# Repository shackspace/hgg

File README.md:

migrated to new location: https://codeberg.org/shackspace/hgg

hackerspace global grid
=======================

More documentation at [hgg.aero](http://hgg.aero/)

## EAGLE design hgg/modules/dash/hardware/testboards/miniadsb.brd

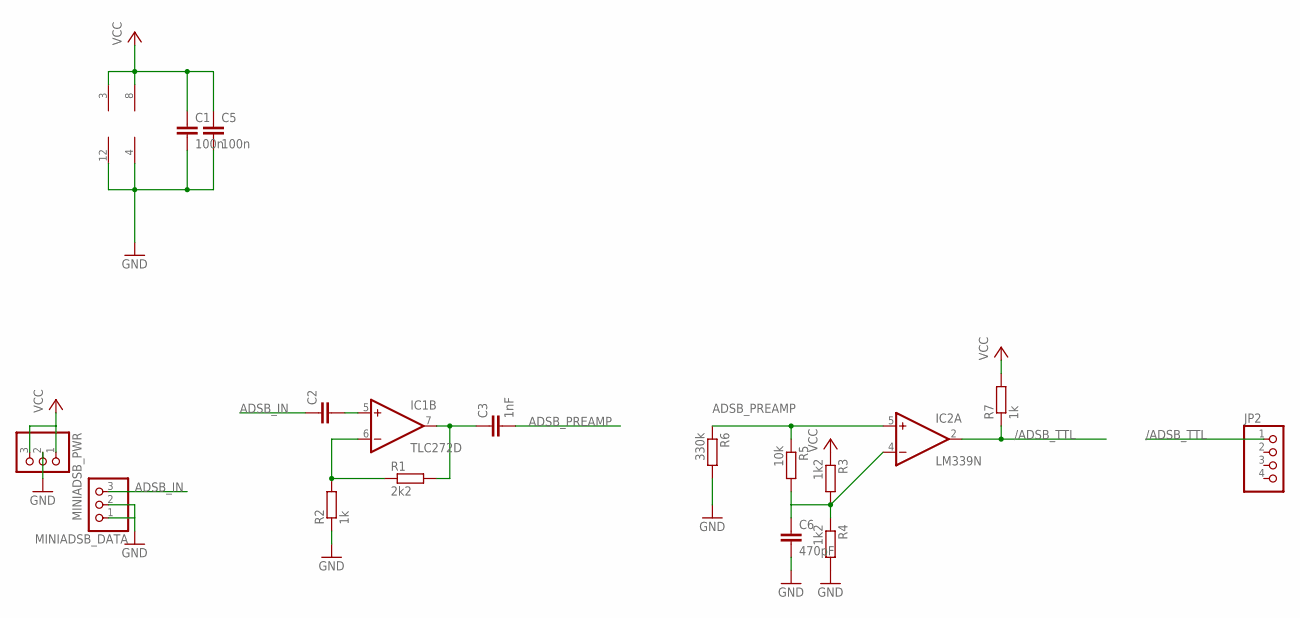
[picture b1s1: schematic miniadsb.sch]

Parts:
C1, C5: 100n; C0805
C2: C-EUC0805; C0805
C3: 1nF; C0805
C6: 470pF; C0805
IC1: TLC272D; SO08
IC2: LM339N; DIL14
JP2: PINHD-1X4; 1X04
MINIADSB_DATA: PINHD-1X3; 1X03
MINIADSB_PWR: PINHD-1X3; 1X03
R1: 2k2; R0805
R2: 1k; R0805
R3, R4: 1k2; R0805
R5: 10k; R0805
R6: 330k; R0805
R7: 1k; R0603

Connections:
/ADSB_TTL: IC2.2 (OUT), JP2.1, R7.1
ADSB_IN: C2.1, MINIADSB_DATA.3
ADSB_PREAMP: C3.2, IC2.5 (+IN), R5.1, R6.1
GND: C1.2, C5.2, C6.2, IC1.4 (V-), IC2.12 (GND), MINIADSB_DATA.1, MINIADSB_DATA.2, MINIADSB_PWR.2, R2.1, R4.2, R6.2
unnamed: C2.2, IC1.5 (+IN)
unnamed: C3.1, IC1.7 (OUT), R1.2
unnamed: IC1.6 (-IN), R1.1, R2.2
unnamed: C6.1, IC2.4 (-IN), R3.2, R4.1, R5.2
VCC: C1.1, C5.1, IC1.8 (V+), IC2.3 (V+), MINIADSB_PWR.1, MINIADSB_PWR.3, R3.1, R7.2

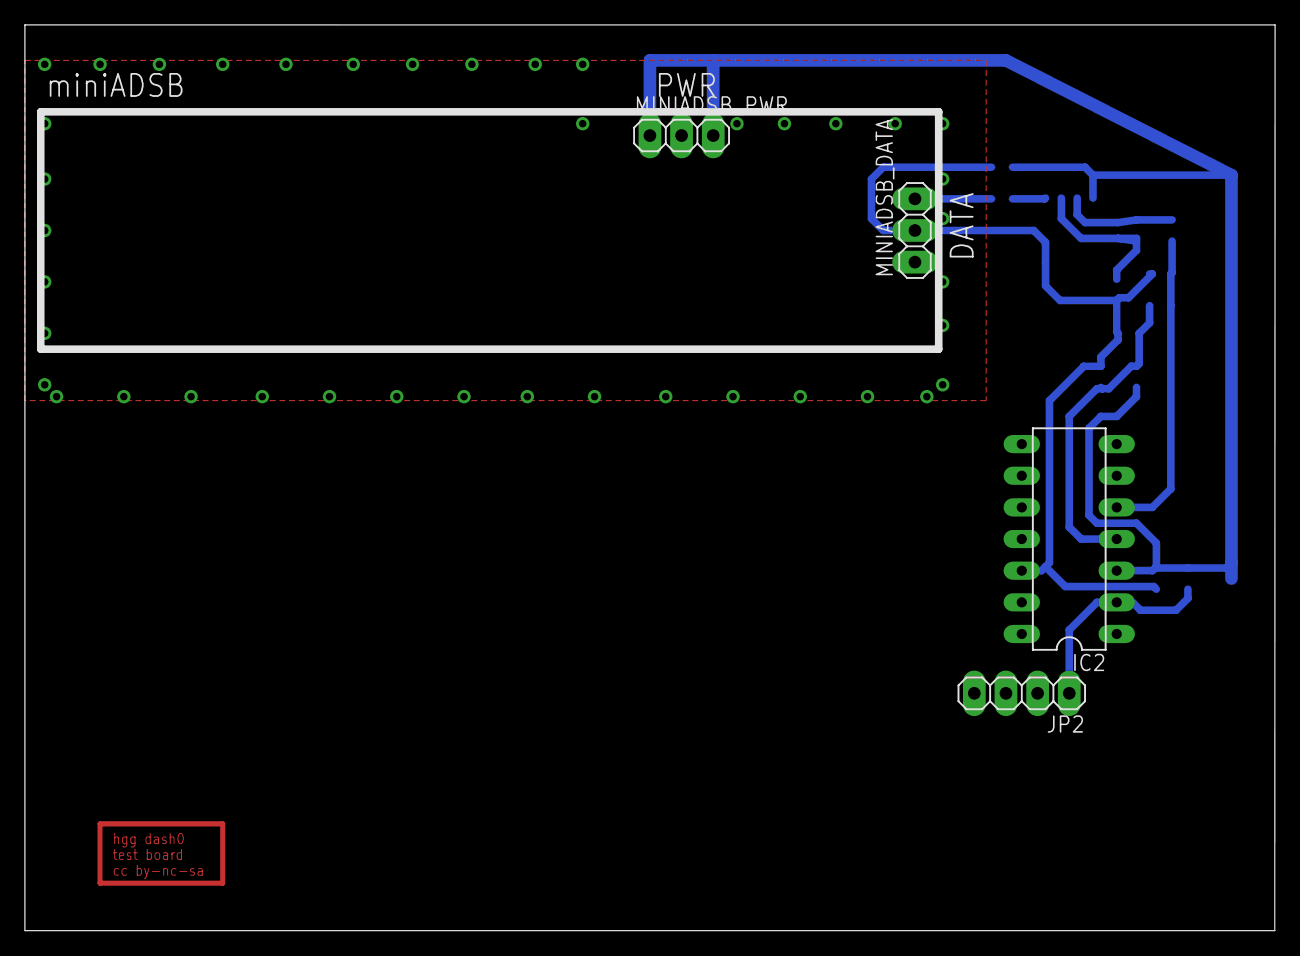
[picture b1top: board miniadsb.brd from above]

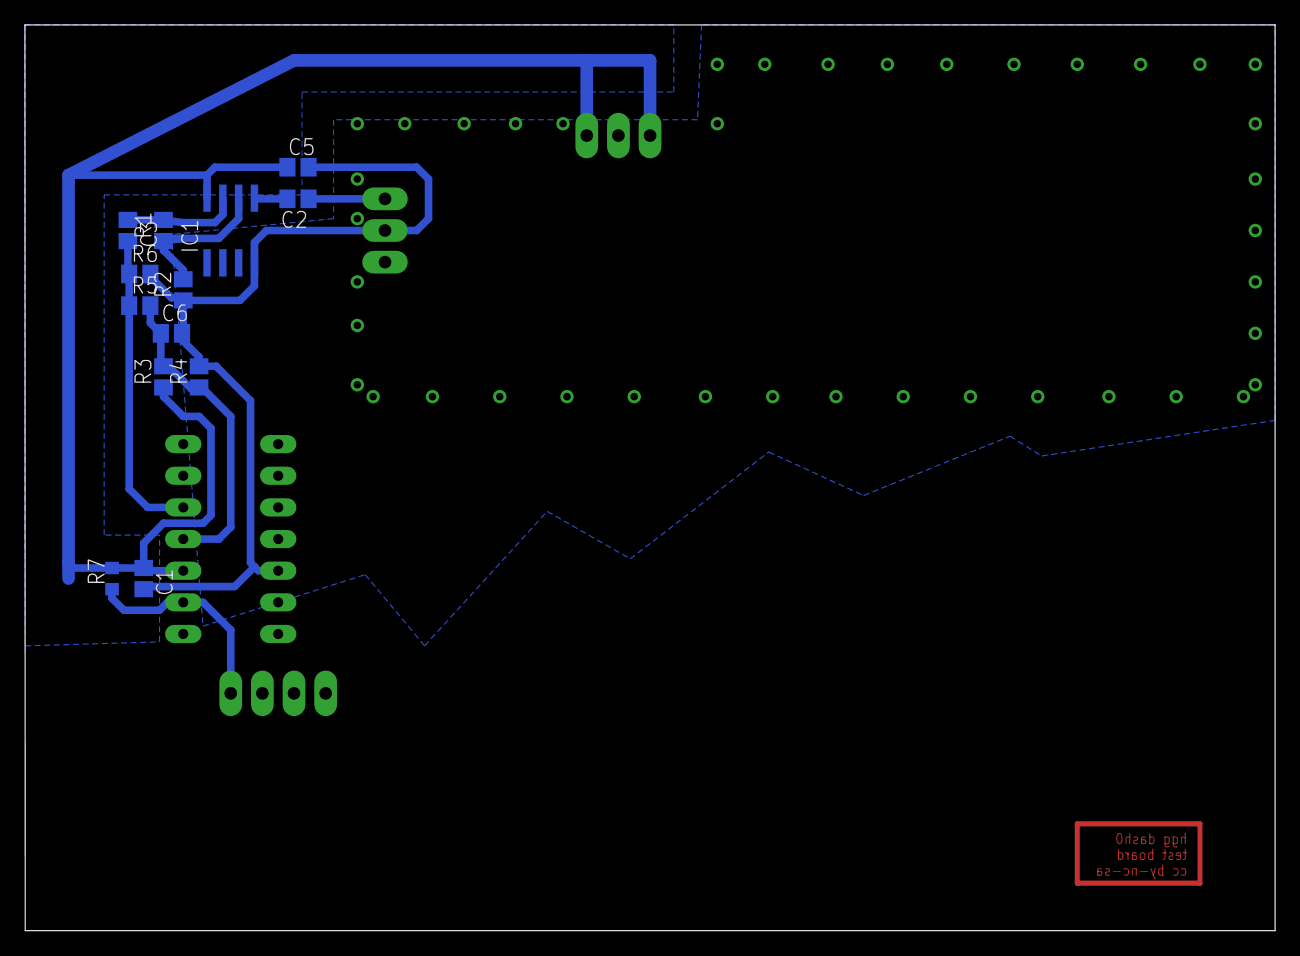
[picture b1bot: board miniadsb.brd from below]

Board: 2 copper layers, 100.3 x 72.7 mm, 17 parts (13 on the bottom side), 9 nets.

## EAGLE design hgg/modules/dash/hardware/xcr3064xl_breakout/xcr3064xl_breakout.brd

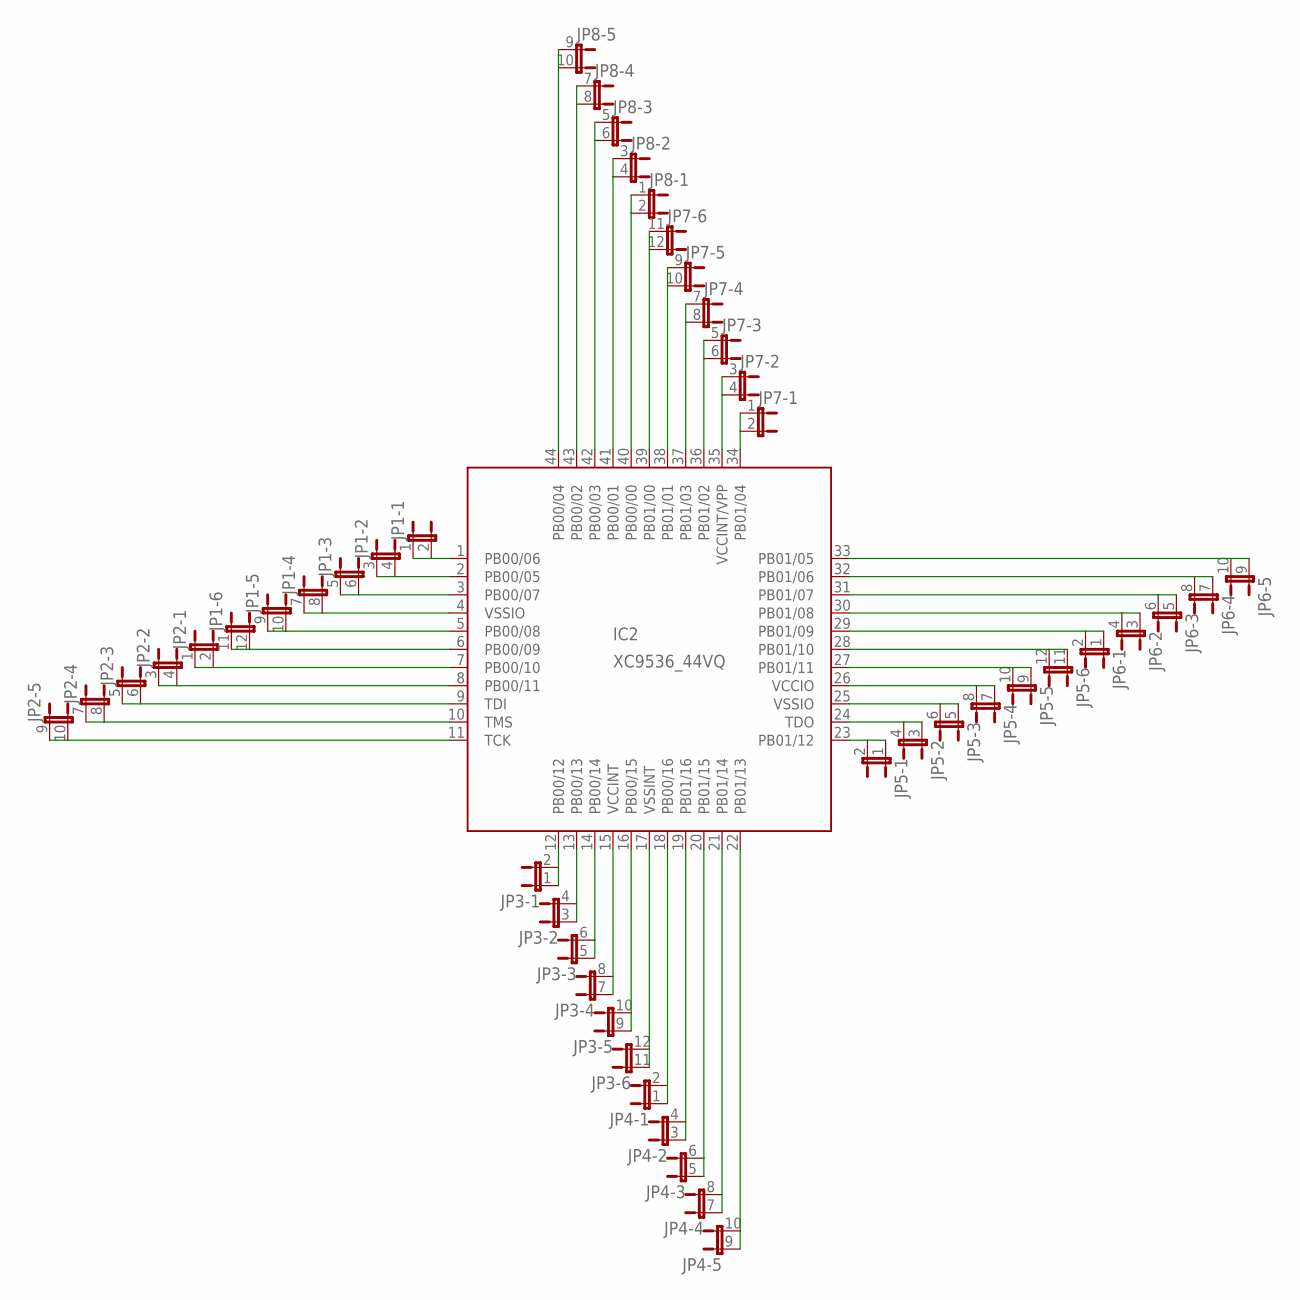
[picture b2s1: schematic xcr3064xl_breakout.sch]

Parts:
IC2: XC9536_44VQ; SQFP-S-10X10-44
JP1, JP2, JP3, JP4, JP5, JP6, JP7, JP8: JP6QE; JP6Q

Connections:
unnamed: IC2.1 (PB00/06), JP1.1, JP1.2
unnamed: IC2.2 (PB00/05), JP1.3 (1), JP1.4 (2)
unnamed: IC2.3 (PB00/07), JP1.5 (1), JP1.6 (2)
unnamed: IC2.4 (VSSIO), JP1.7 (1), JP1.8 (2)
unnamed: IC2.5 (PB00/08), JP1.9 (1), JP1.10 (2)
unnamed: IC2.6 (PB00/09), JP1.11 (1), JP1.12 (2)
unnamed: IC2.7 (PB00/10), JP2.1, JP2.2
unnamed: IC2.8 (PB00/11), JP2.3 (1), JP2.4 (2)
unnamed: IC2.9 (TDI), JP2.5 (1), JP2.6 (2)
unnamed: IC2.10 (TMS), JP2.7 (1), JP2.8 (2)
unnamed: IC2.11 (TCK), JP2.9 (1), JP2.10 (2)
unnamed: IC2.12 (PB00/12), JP3.1, JP3.2
unnamed: IC2.13 (PB00/13), JP3.3 (1), JP3.4 (2)
unnamed: IC2.14 (PB00/14), JP3.5 (1), JP3.6 (2)
unnamed: IC2.15 (VCCINT), JP3.7 (1), JP3.8 (2)
unnamed: IC2.16 (PB00/15), JP3.9 (1), JP3.10 (2)
unnamed: IC2.17 (VSSINT), JP3.11 (1), JP3.12 (2)
unnamed: IC2.18 (PB00/16), JP4.1, JP4.2
unnamed: IC2.19 (PB01/16), JP4.3 (1), JP4.4 (2)
unnamed: IC2.20 (PB01/15), JP4.5 (1), JP4.6 (2)
unnamed: IC2.21 (PB01/14), JP4.7 (1), JP4.8 (2)
unnamed: IC2.22 (PB01/13), JP4.9 (1), JP4.10 (2)
unnamed: IC2.23 (PB01/12), JP5.1, JP5.2
unnamed: IC2.24 (TDO), JP5.3 (1), JP5.4 (2)
unnamed: IC2.25 (VSSIO), JP5.5 (1), JP5.6 (2)
unnamed: IC2.26 (VCCIO), JP5.7 (1), JP5.8 (2)
unnamed: IC2.27 (PB01/11), JP5.9 (1), JP5.10 (2)
unnamed: IC2.28 (PB01/10), JP5.11 (1), JP5.12 (2)
unnamed: IC2.29 (PB01/09), JP6.1, JP6.2
unnamed: IC2.30 (PB01/08), JP6.3 (1), JP6.4 (2)
unnamed: IC2.31 (PB01/07), JP6.5 (1), JP6.6 (2)
unnamed: IC2.32 (PB01/06), JP6.7 (1), JP6.8 (2)
unnamed: IC2.33 (PB01/05), JP6.9 (1), JP6.10 (2)
unnamed: IC2.34 (PB01/04), JP7.1, JP7.2
unnamed: IC2.35 (VCCINT/VPP), JP7.3 (1), JP7.4 (2)
unnamed: IC2.36 (PB01/02), JP7.5 (1), JP7.6 (2)
unnamed: IC2.37 (PB01/03), JP7.7 (1), JP7.8 (2)
unnamed: IC2.38 (PB01/01), JP7.9 (1), JP7.10 (2)
unnamed: IC2.39 (PB01/00), JP7.11 (1), JP7.12 (2)
unnamed: IC2.40 (PB00/00), JP8.1, JP8.2
unnamed: IC2.41 (PB00/01), JP8.3 (1), JP8.4 (2)
unnamed: IC2.42 (PB00/03), JP8.5 (1), JP8.6 (2)
unnamed: IC2.43 (PB00/02), JP8.7 (1), JP8.8 (2)
unnamed: IC2.44 (PB00/04), JP8.9 (1), JP8.10 (2)

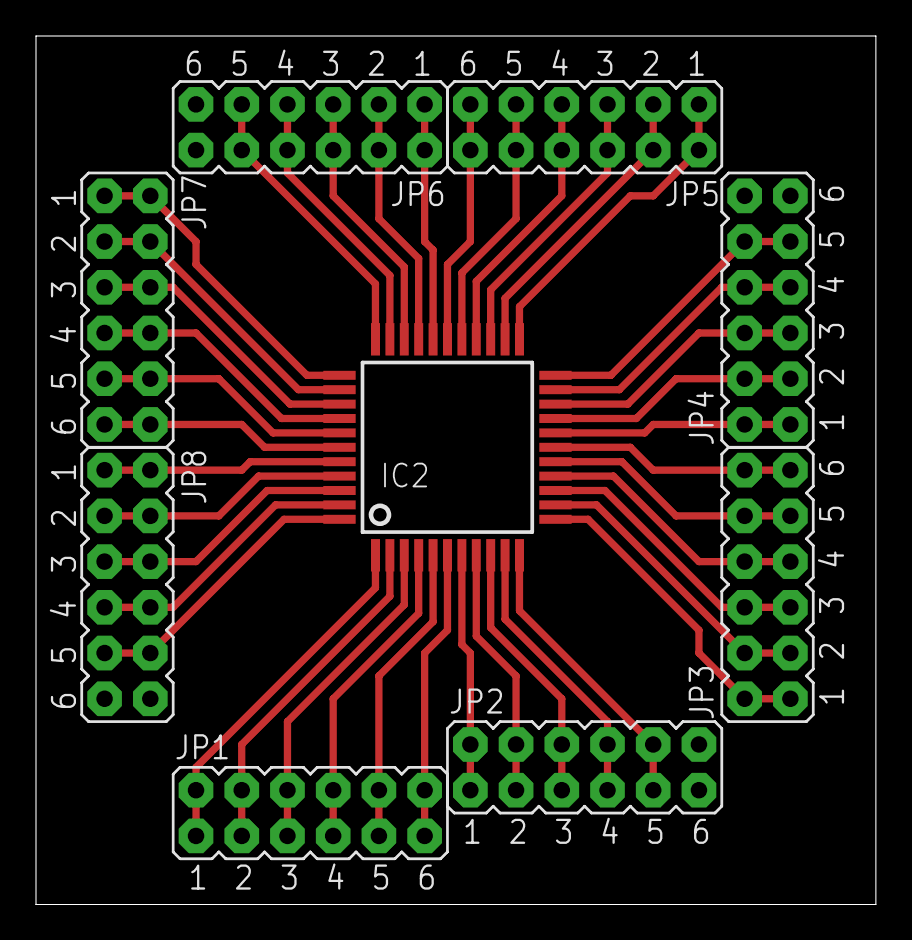
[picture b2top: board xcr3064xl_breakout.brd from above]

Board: 2 copper layers, 46.7 x 48.2 mm, 9 parts (0 on the bottom side), 44 nets.

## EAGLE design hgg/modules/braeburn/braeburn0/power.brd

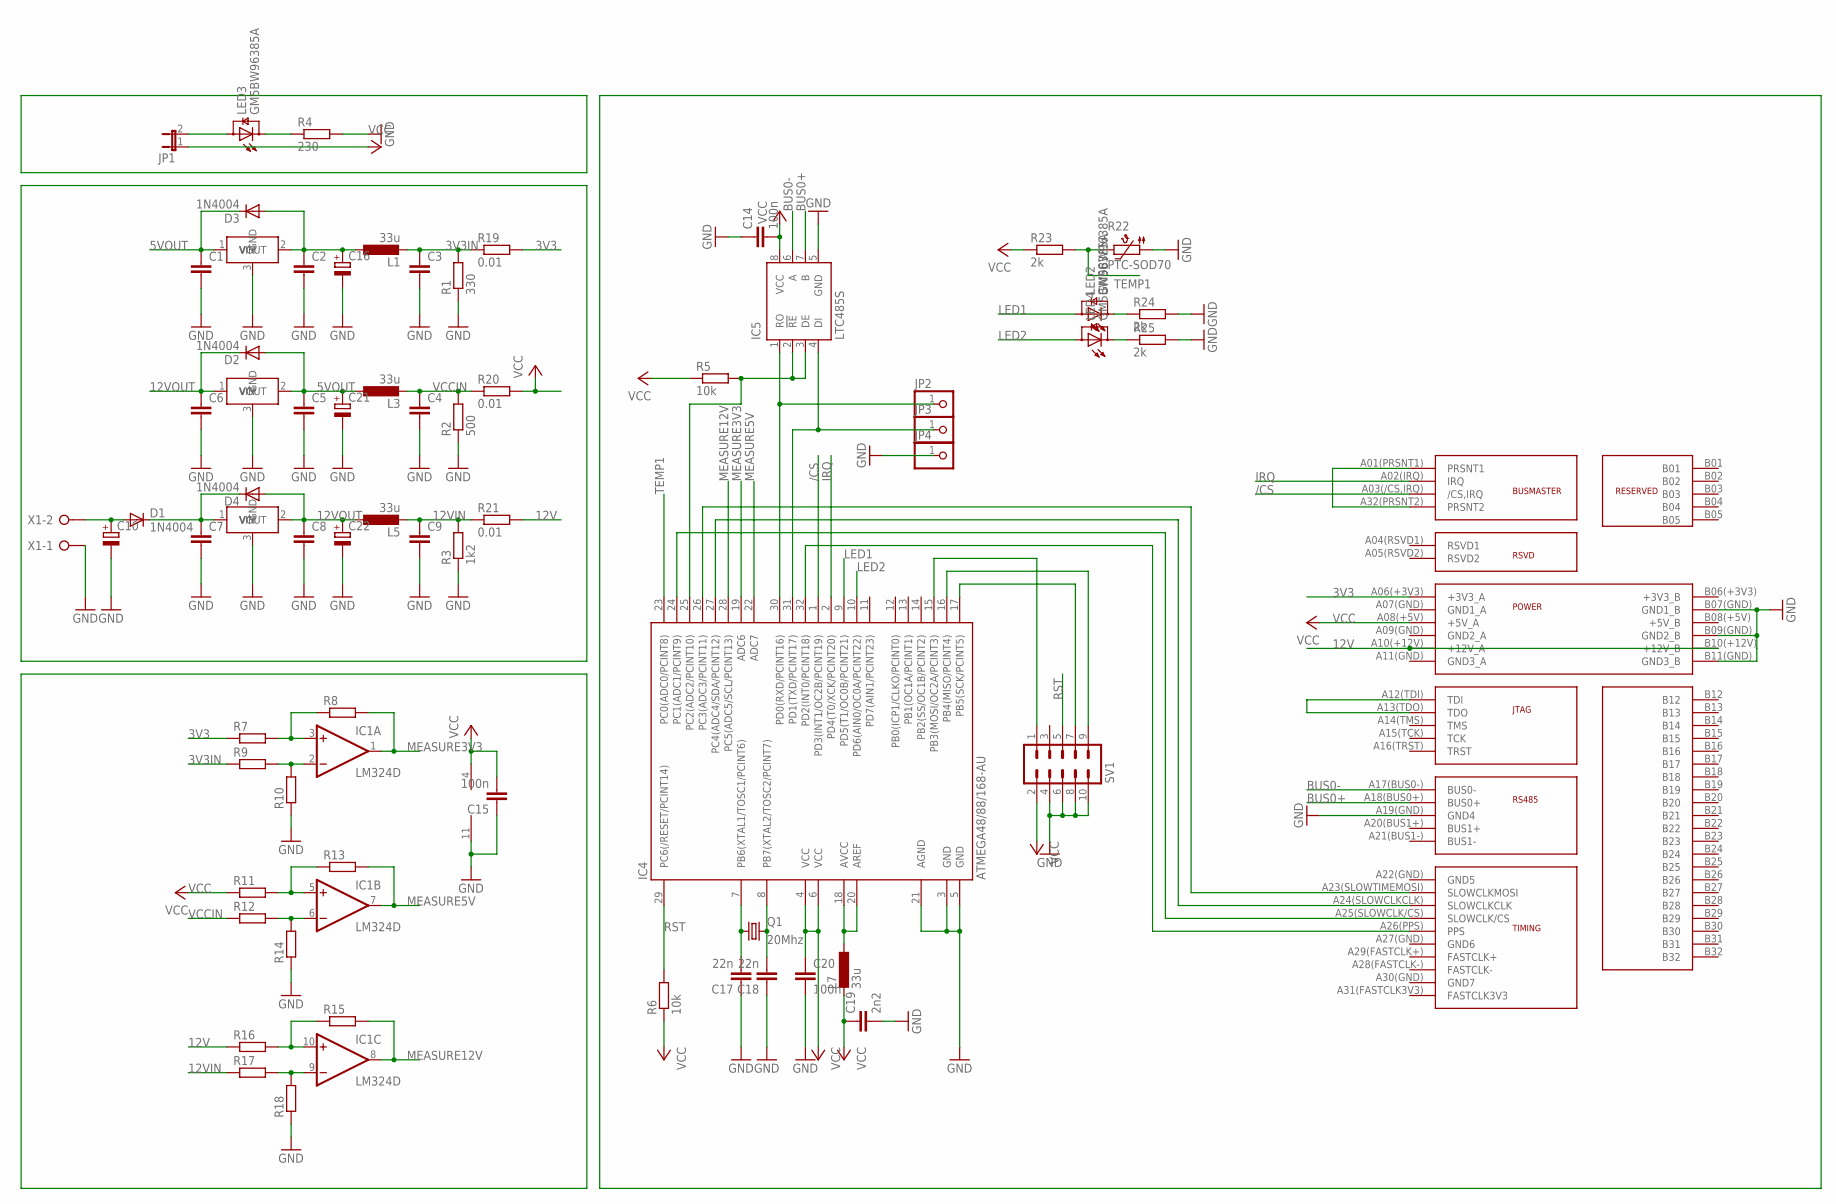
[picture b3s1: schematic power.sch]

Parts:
C1, C2, C3, C4, C5, C6, C7, C8, C9: C-EUC0805; C0805
C10: CPOL-EU150CLZ-1010; 150CLZ-1010
C14, C15, C20: 100n; C0603
C16, C21, C22: CPOL-EU153CLV-0505; 153CLV-0505
C17, C18: 22n; C0603
C19: 2n2; C0603
D1, D2, D3, D4: 1N4004; DO41-10
IC1: LM324D; SO14
IC4: ATMEGA48/88/168-AU; TQFP32-08
IC5: LTC485S; SOIC8
JP1: JP1E; JP1
JP2, JP3, JP4: PINHD-1X1; 1X01
L1, L3, L5, L7: 33u; 0207/5V
LED2, LED3, LED4: GM5BW96385A
Q1: 20Mhz; HC49UP
R1: 330; R0805
R2: 500; R0603
R3: 1k2; R0603
R4: 230; R0603
R5, R6: 10k; R0603
R7, R8, R9, R10, R11, R12, R13, R14, R15, R16, R17, R18: R-EU_R0603; R0603
R19, R20, R21: 0.01; 0207/15
R22: PTC-SOD70; SOD70
R23, R24, R25: 2k; R0603
SV1: MA05-2
U$1: FRIENDSHIPCONNECTOR; FRIENDSHIP_EDGE_CONNECTOR
U$2, U$3, U$4: AP1084; TO263
X1: W237-02P; W237-132

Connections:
3V3: R7.1, R19.2, U$1.A06(+3V3) (+3V3_A)
3V3IN: C3.1, L1.2, R1.2, R9.1, R19.1
5VOUT: C1.1, C5.1, C21.+, D2.A, D3.C, L3.1, U$2.1 (VIN), U$3.2 (VOUT)
12V: R16.1, R21.2, U$1.A10(+12V) (+12V_A), U$1.B10(+12V) (+12V_B)
12VIN: C9.1, L5.2, R3.2, R17.1, R21.1
12VOUT: C6.1, C8.1, C22.+, D2.C, D4.A, L5.1, U$3.1 (VIN), U$4.2 (VOUT)
/CS: IC4.1 (PD3(INT1/OC2B/PCINT19)), U$1.A03(/CS,IRQ) (/CS,IRQ)
BUS0+: IC5.7 (B), U$1.A18(BUS0+) (BUS0+)
BUS0-: IC5.6 (A), U$1.A17(BUS0-) (BUS0-)
GND: C1.2, C2.2, C3.2, C4.2, C5.2, C6.2, C7.2, C8.2, C9.2, C10.-, C14.1, C15.1, C16.-, C17.1, C18.1, C19.2, C20.2, C21.-, C22.-, IC1.11 (V-), IC4.3 (GND), IC4.5 (GND), IC4.21 (AGND), IC5.5 (GND), JP4.1, R1.1, R2.1, R3.1, R4.2, R10.1, R14.1, R18.1, R22.1, R24.2, R25.2, SV1.4, SV1.6, SV1.8, SV1.10, U$1.A19(GND) (GND4), U$1.B07(GND) (GND1_B), U$1.B09(GND) (GND2_B), U$1.B11(GND) (GND3_B), U$2.3 (GND), U$3.3 (GND), U$4.3 (GND), X1.1
IRQ: IC4.2 (PD4(T0/XCK/PCINT20)), U$1.A02(IRQ) (IRQ)
LED1: IC4.9 (PD5(T1/OC0B/PCINT21)), LED2.A
LED2: IC4.10 (PD6(AIN0/OC0A/PCINT22)), LED4.A
MEASURE3V3: IC1.1 (OUT), IC4.19 (ADC6), R8.2
MEASURE5V: IC1.7 (OUT), IC4.22 (ADC7), R13.2
MEASURE12V: IC1.8 (OUT), IC4.28 (PC5(ADC5/SCL/PCINT13)), R15.2
unnamed: C18.2, IC4.8 (PB7(XTAL2/TOSC2/PCINT7)), Q1.2
unnamed: C2.1, C16.+, D3.A, L1.1, U$2.2 (VOUT)
unnamed: IC4.24 (PC1(ADC1/PCINT9)), U$1.A25(SLOWCLK/CS) (SLOWCLK/CS)
unnamed: IC1.2 (-IN), R9.2, R10.2
unnamed: IC1.3 (+IN), R7.2, R8.1
unnamed: JP1.2, LED3.A
unnamed: C7.1, D1.C, D4.C, U$4.1 (VIN)
unnamed: C10.+, D1.A, X1.2
unnamed: C17.2, IC4.7 (PB6(XTAL1/TOSC1/PCINT6)), Q1.1
unnamed: IC1.6 (-IN), R12.2, R14.2
unnamed: IC4.18 (AVCC), IC4.20 (AREF), L7.1
unnamed: IC4.16 (PB4(MISO/PCINT4)), SV1.9
unnamed: IC4.17 (PB5(SCK/PCINT5)), SV1.7
unnamed: IC4.15 (PB3(MOSI/OC2A/PCINT3)), SV1.1
unnamed: LED3.C, R4.1
unnamed: IC4.32 (PD2(INT0/PCINT18)), U$1.A26(PPS) (PPS)
unnamed: IC4.31 (PD1(TXD/PCINT17)), IC5.4 (DI), JP3.1
unnamed: IC1.5 (+IN), R11.2, R13.1
unnamed: U$1.A01(PRSNT1) (PRSNT1), U$1.A32(PRSNT2) (PRSNT2)
unnamed: IC4.27 (PC4(ADC4/SDA/PCINT12)), U$1.A24(SLOWCLKCLK) (SLOWCLKCLK)
unnamed: IC4.26 (PC3(ADC3/PCINT11)), U$1.A23(SLOWTIMEMOSI) (SLOWCLKMOSI)
unnamed: IC1.10 (+IN), R15.1, R16.2
unnamed: IC1.9 (-IN), R17.2, R18.2
unnamed: U$1.A12(TDI) (TDI), U$1.A13(TDO) (TDO)
unnamed: IC4.30 (PD0(RXD/PCINT16)), IC5.1 (RO), JP2.1
unnamed: IC4.25 (PC2(ADC2/PCINT10)), IC5.2 (!RE), IC5.3 (DE), R5.2
unnamed: LED2.C, R24.1
unnamed: LED4.C, R25.1
RST: IC4.29 (PC6(/RESET/PCINT14)), R6.2, SV1.5
TEMP1: IC4.23 (PC0(ADC0/PCINT8)), R22.2, R23.2
VCC: C14.2, C15.2, C19.1, C20.1, IC1.4 (V+), IC4.4 (VCC), IC4.6 (VCC), IC5.8 (VCC), JP1.1, L7.2, R5.1, R6.1, R11.1, R20.2, R23.1, SV1.2, U$1.A08(+5V) (+5V_A)
VCCIN: C4.1, L3.2, R2.2, R12.1, R20.1

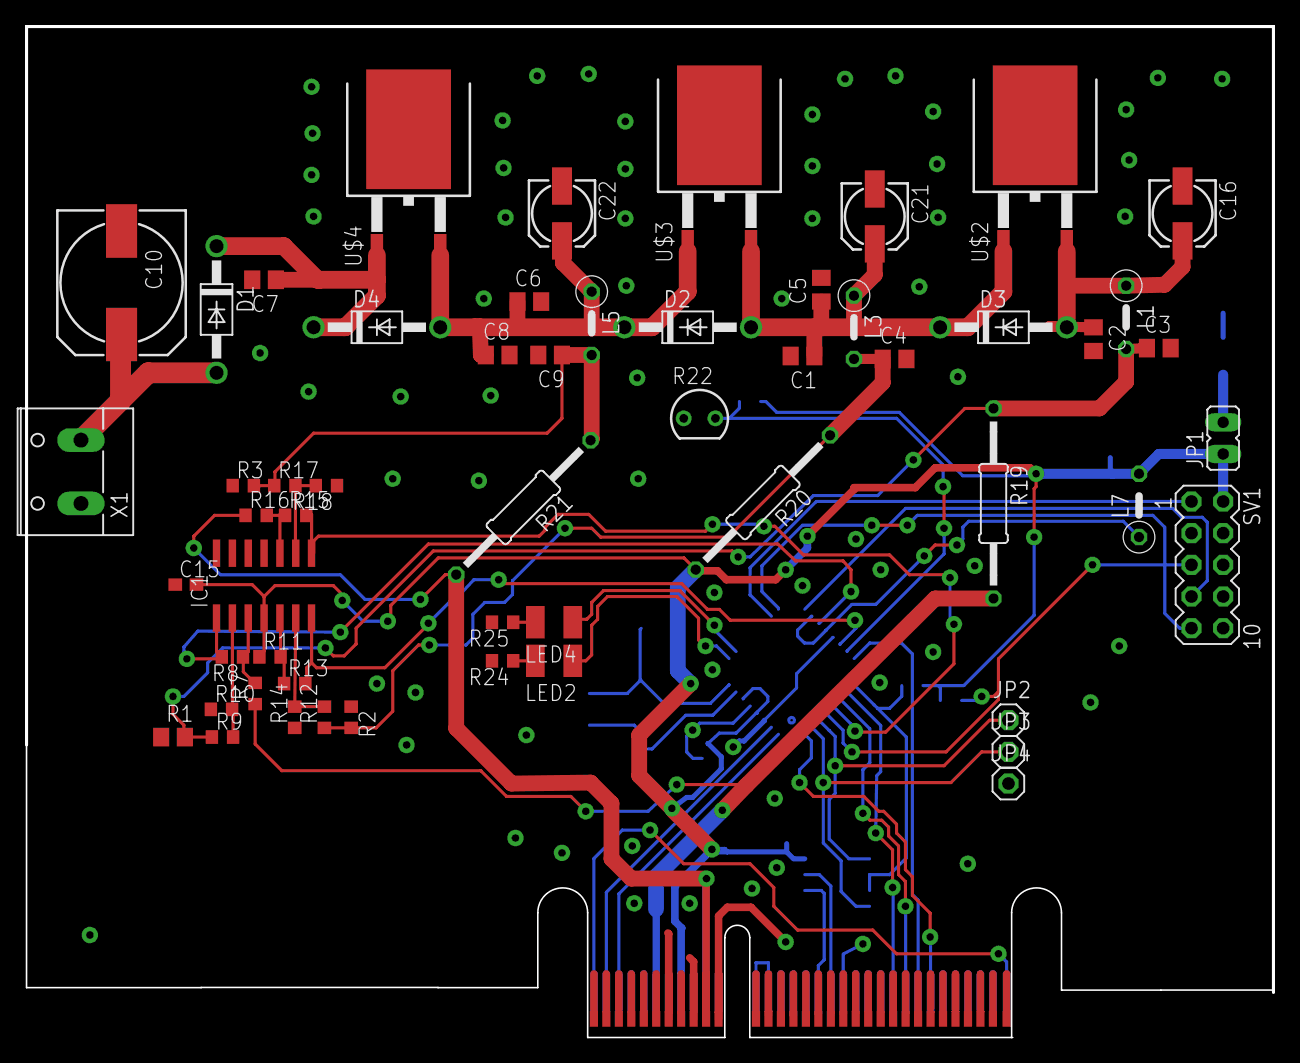
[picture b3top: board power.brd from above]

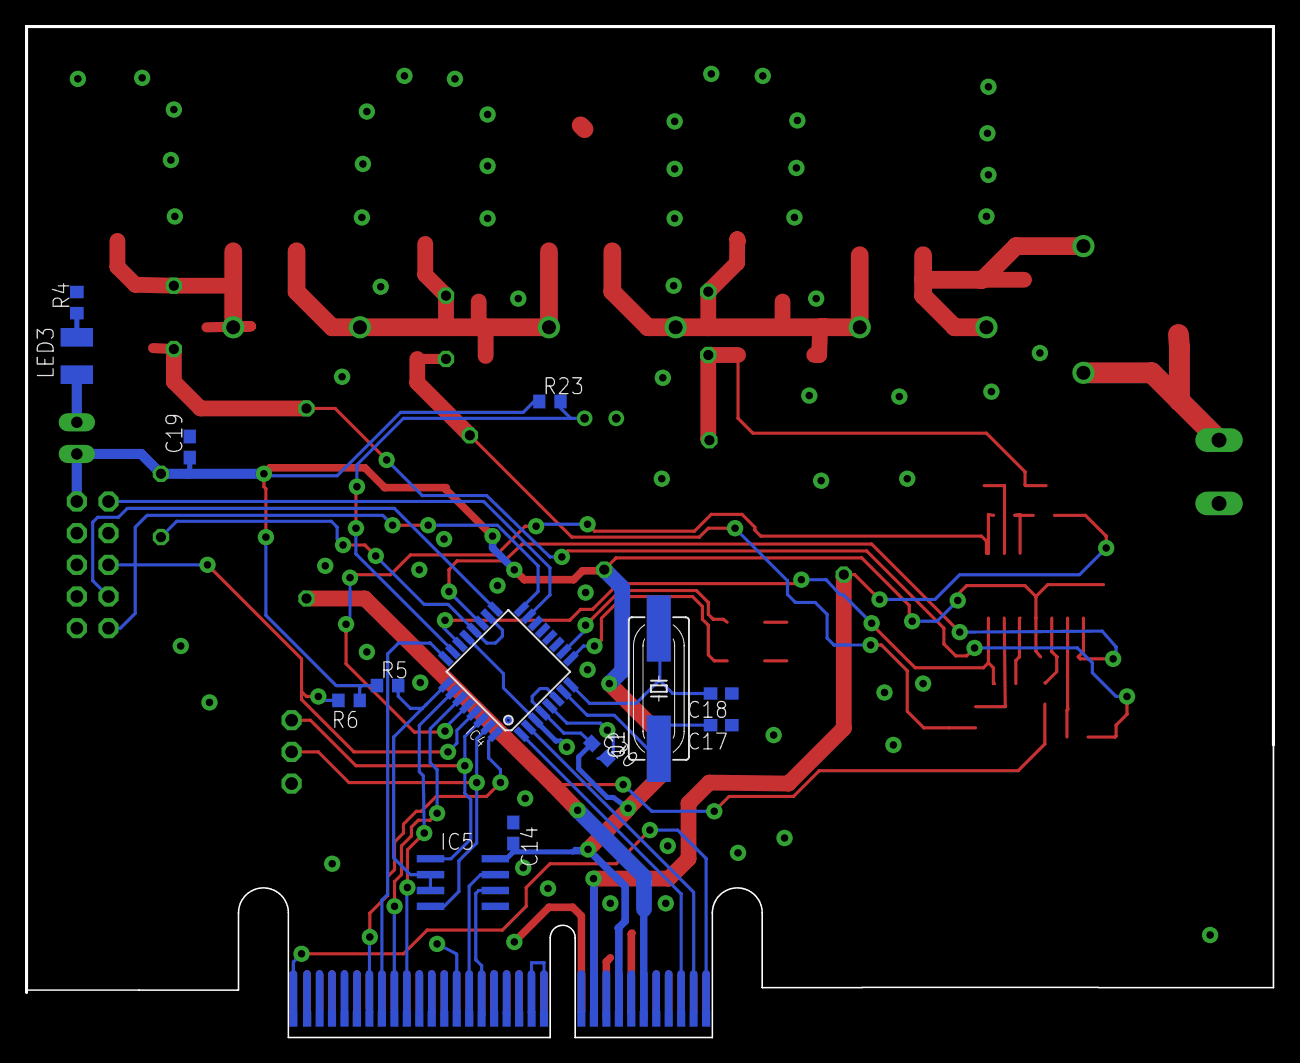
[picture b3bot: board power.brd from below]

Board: 2 copper layers, 100.0 x 81.1 mm, 69 parts (13 on the bottom side), 48 nets.

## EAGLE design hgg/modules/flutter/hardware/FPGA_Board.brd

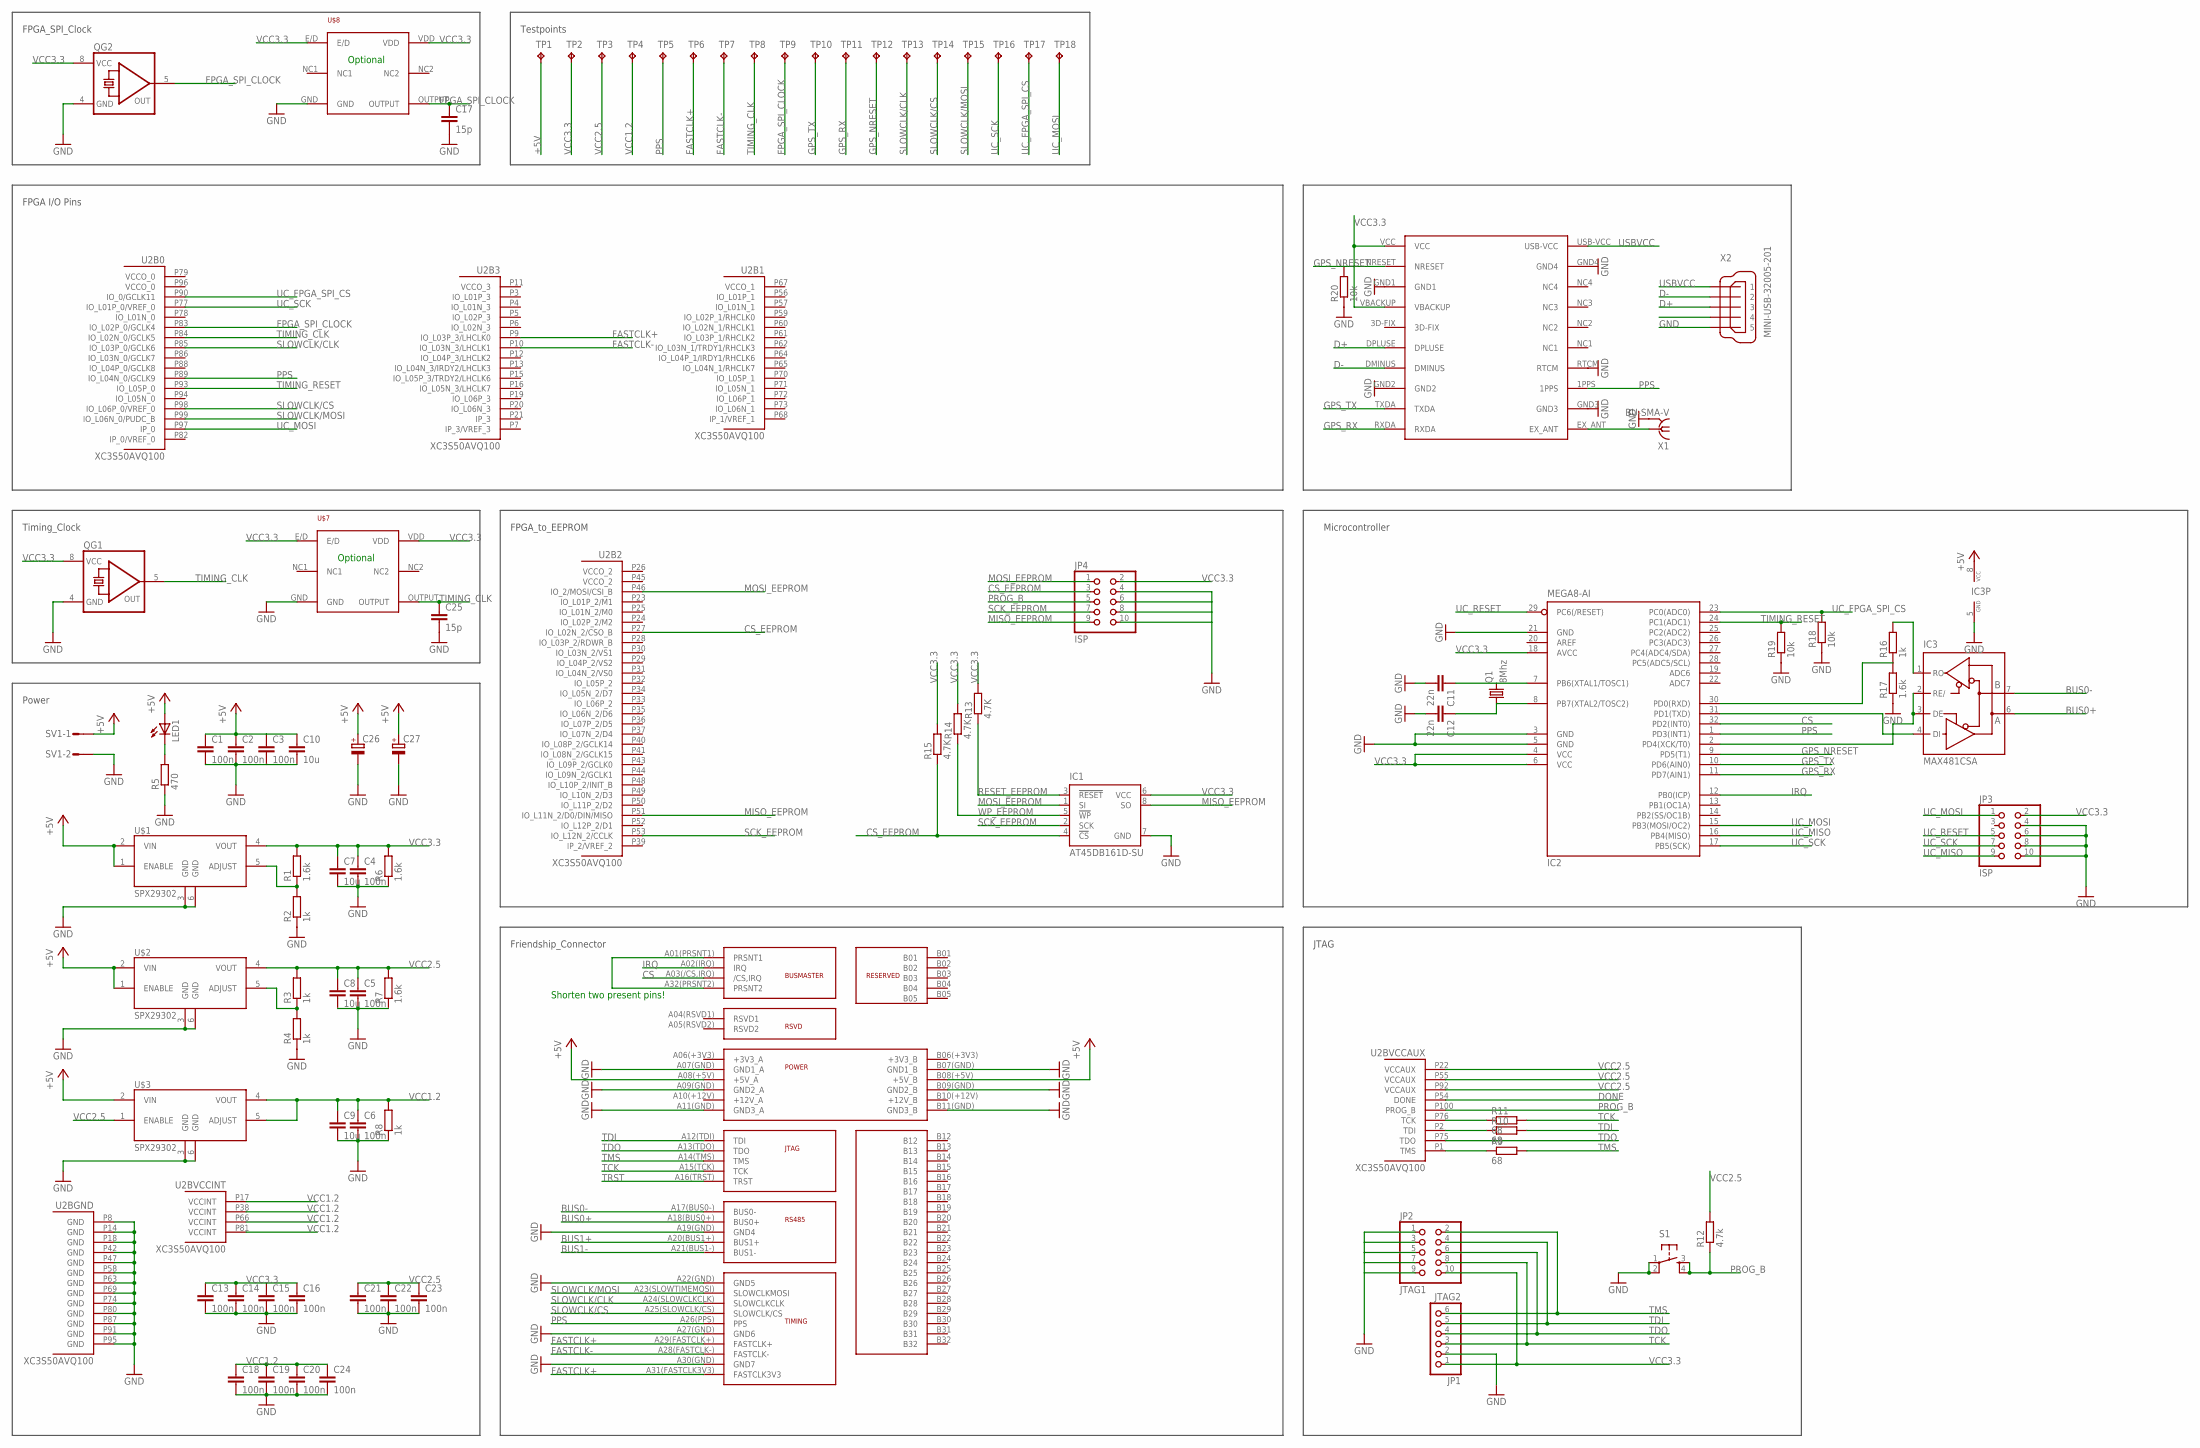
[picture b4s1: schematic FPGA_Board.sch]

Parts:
C1, C2, C3, C4, C5, C6, C13, C14, C15, C16, C18, C19, C20, C21, C22, C23, C24: 100n; C0603
C7, C8, C9, C10: 10u; C0603
C11, C12: 22n; C0603
C17, C25: 15p; C0603
C26, C27: CPOL-EUE5-8.5; E5-8,5
IC1: AT45DB161D-SU; 8S2
IC2: MEGA8-AI; TQFP32-08
IC3: MAX481CSA; SO08
JP1: JTAG2; 1X06
JP2: JTAG1; 2X05
JP3, JP4: ISP; 2X05
LED1: LEDCHIPLED_0805; CHIPLED_0805
Q1: 8Mhz; SM49
QG1, QG2: QG5460; DIL08S
R1, R6, R7, R17: 1.6k; R0603
R2, R3, R4, R8, R16: 1k; R0603
R5: 470; R0603
R9, R10, R11: 68; R0603
R12: 4.7k; R0603
R13, R14, R15: 4.7K; R0603
R18, R19, R20: 10k; R0603
S1: TAC_SWITCHPTH; TACTILE-PTH
SV1: L02P
TP1, TP2, TP3, TP4, TP5, TP6, TP7, TP8, TP9, TP10, TP11, TP12, TP13, TP14, TP15, TP16, TP17, TP18: TPB2,54; B2,54
U2: XC3S50AVQ100; VQ100
U$1, U$2, U$3: SPX29302; Q5-DD_SPX29300
U$4: FRIENDSHIPCONNECTOR; FRIENDSHIP_EDGE_CONNECTOR
U$5: HGG_LOGO
U$6: GPS
U$7, U$8: OSCILLATOR
X1: BU-SMA-V
X2: MINI-USB-32005-201; 32005-201

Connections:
+5V: C1.1, C2.1, C3.1, C10.1, C26.+, C27.+, IC3.8 (VCC), LED1.A, SV1.1, TP1.TP, U$1.1 (ENABLE), U$1.2 (VIN), U$2.1 (ENABLE), U$2.2 (VIN), U$3.2 (VIN), U$4.A08(+5V) (+5V_A), U$4.B08(+5V) (+5V_B)
BUS0+: IC3.6 (A), U$4.A18(BUS0+) (BUS0+)
BUS0-: IC3.7 (B), U$4.A17(BUS0-) (BUS0-)
BUS1+: U$4.A20(BUS1+) (BUS1+)
BUS1-: U$4.A21(BUS1-) (BUS1-)
CS: IC2.32 (PD2(INT0)), U$4.A03(/CS,IRQ) (/CS,IRQ)
CS_EEPROM: IC1.4 (!CS), JP4.3, R15.1, U2.P27 (IO_L02N_2/CSO_B)
D+: U$6.DPLUSE, X2.3
D-: U$6.DMINUS, X2.2
DI: IC2.31 (PD1(TXD)), IC3.4 (DI)
DONE: U2.P54 (DONE)
FASTCLK+: TP6.TP, U2.P9 (IO_L03P_3/LHCLK0), U$4.A29(FASTCLK+) (FASTCLK+), U$4.A31(FASTCLK3V3) (FASTCLK3V3)
FASTCLK-: TP7.TP, U2.P10 (IO_L03N_3/LHCLK1), U$4.A28(FASTCLK-) (FASTCLK-)
FPGA_SPI_CLOCK: C17.1, QG2.5 (OUT), TP9.TP, U2.P83 (IO_L02P_0/GCLK4), U$8.OUTPUT
GND: C1.2, C2.2, C3.2, C4.2, C5.2, C6.2, C7.2, C8.2, C9.2, C10.2, C11.2, C12.2, C13.2, C14.2, C15.2, C16.2, C17.2, C18.2, C19.2, C20.2, C21.2, C22.2, C23.2, C24.2, C25.2, C26.-, C27.-, IC1.7 (GND), IC2.3 (GND), IC2.5 (GND), IC2.21 (GND), IC3.5 (GND), JP1.2, JP2.1, JP2.3, JP2.5, JP2.7, JP2.9, JP3.4, JP3.6, JP3.8, JP3.10, JP4.4, JP4.6, JP4.8, JP4.10, QG1.4 (GND), QG2.4 (GND), R2.1, R4.1, R5.1, R6.1, R7.1, R8.1, R17.1, R18.1, R19.1, R20.1, S1.1, S1.2, SV1.2, U2.P8 (GND), U2.P14 (GND), U2.P18 (GND), U2.P42 (GND), U2.P47 (GND), U2.P58 (GND), U2.P63 (GND), U2.P69 (GND), U2.P74 (GND), U2.P80 (GND), U2.P87 (GND), U2.P91 (GND), U2.P95 (GND), U$1.3 (GND), U$1.6 (GND), U$2.3 (GND), U$2.6 (GND), U$3.3 (GND), U$3.6 (GND), U$4.A07(GND) (GND1_A), U$4.A09(GND) (GND2_A), U$4.A11(GND) (GND3_A), U$4.A19(GND) (GND4), U$4.A22(GND) (GND5), U$4.A27(GND) (GND6), U$4.A30(GND) (GND7), U$4.B07(GND) (GND1_B), U$4.B09(GND) (GND2_B), U$4.B11(GND) (GND3_B), U$6.GND1, U$6.GND2, U$6.GND3, U$6.GND4, U$6.RTCM, U$7.GND, U$8.GND, X1.2 (GND), X1.3 (GND), X1.4 (GND), X1.5 (GND), X2.5
GPS_NRESET: IC2.9 (PD5(T1)), R20.2, TP12.TP, U$6.NRESET
GPS_RX: IC2.11 (PD7(AIN1)), TP11.TP, U$6.RXDA
GPS_TX: IC2.10 (PD6(AIN0)), TP10.TP, U$6.TXDA
IRQ: IC2.12 (PB0(ICP)), U$4.A02(IRQ) (IRQ)
MISO_EEPROM: IC1.8 (SO), JP4.9, U2.P51 (IO_L11N_2/D0/DIN/MISO)
MOSI_EEPROM: IC1.1 (SI), JP4.1, U2.P46 (IO_2/MOSI/CSI_B)
unnamed: R11.1, U2.P76 (TCK)
unnamed: R10.1, U2.P2 (TDI)
unnamed: LED1.C, R5.2
unnamed: R9.1, U2.P1 (TMS)
unnamed: IC2.2 (PD4(XCK/T0)), IC3.2 (RE/), IC3.3 (DE)
unnamed: IC2.30 (PD0(RXD)), R16.1, R17.2
unnamed: R1.1, R2.2, U$1.5 (ADJUST)
unnamed: R3.1, R4.2, U$2.5 (ADJUST)
unnamed: IC3.1 (RO), R16.2
unnamed: C11.1, IC2.7 (PB6(XTAL1/TOSC1)), Q1.2
unnamed: C12.1, IC2.8 (PB7(XTAL2/TOSC2)), Q1.1
unnamed: U$4.A01(PRSNT1) (PRSNT1), U$4.A32(PRSNT2) (PRSNT2)
unnamed: U$6.EX_ANT, X1.1
PPS: IC2.1 (PD3(INT1)), TP5.TP, U2.P89 (IO_L04N_0/GCLK9), U$4.A26(PPS) (PPS), U$6.1PPS
PROG_B: JP4.5, R12.1, S1.3, S1.4, U2.P100 (PROG_B)
RESET_EEPROM: IC1.3 (!RESET), R13.1
SCK_EEPROM: IC1.2 (SCK), JP4.7, U2.P53 (IO_L12N_2/CCLK)
SLOWCLK/CLK: TP13.TP, U2.P85 (IO_L03P_0/GCLK6), U$4.A24(SLOWCLKCLK) (SLOWCLKCLK)
SLOWCLK/CS: TP14.TP, U2.P98 (IO_L06P_0/VREF_0), U$4.A25(SLOWCLK/CS) (SLOWCLK/CS)
SLOWCLK/MOSI: TP15.TP, U2.P99 (IO_L06N_0/PUDC_B), U$4.A23(SLOWTIMEMOSI) (SLOWCLKMOSI)
TCK: JP1.3, JP2.8, R11.2, U$4.A15(TCK) (TCK)
TDI: JP1.5, JP2.4, R10.2, U$4.A12(TDI) (TDI)
TDO: JP1.4, JP2.6, U2.P75 (TDO), U$4.A13(TDO) (TDO)
TIMING_CLK: C25.1, QG1.5 (OUT), TP8.TP, U2.P84 (IO_L02N_0/GCLK5), U$7.OUTPUT
TIMING_RESET: IC2.24 (PC1(ADC1)), R19.2, U2.P93 (IO_L05P_0)
TMS: JP1.6, JP2.2, R9.2, U$4.A14(TMS) (TMS)
TRST: U$4.A16(TRST) (TRST)
UC_FPGA_SPI_CS: IC2.23 (PC0(ADC0)), R18.2, TP17.TP, U2.P90 (IO_0/GCLK11)
UC_MISO: IC2.16 (PB4(MISO)), JP3.9
UC_MOSI: IC2.15 (PB3(MOSI/OC2)), JP3.1, TP18.TP, U2.P97 (IP_0)
UC_RESET: IC2.29 (PC6(/RESET)), JP3.5
UC_SCK: IC2.17 (PB5(SCK)), JP3.7, TP16.TP, U2.P77 (IO_L01P_0/VREF_0)
USBVCC: U$6.USB-VCC, X2.1
VCC1.2: C6.1, C9.1, C18.1, C19.1, C20.1, C24.1, R8.2, TP4.TP, U2.P17 (VCCINT), U2.P38 (VCCINT), U2.P66 (VCCINT), U2.P81 (VCCINT), U$3.4 (VOUT), U$3.5 (ADJUST)
VCC2.5: C5.1, C8.1, C21.1, C22.1, C23.1, R3.2, R7.2, R12.2, TP3.TP, U2.P22 (VCCAUX), U2.P55 (VCCAUX), U2.P92 (VCCAUX), U$2.4 (VOUT), U$3.1 (ENABLE)
VCC3.3: C4.1, C7.1, C13.1, C14.1, C15.1, C16.1, IC1.6 (VCC), IC2.4 (VCC), IC2.6 (VCC), IC2.18 (AVCC), JP1.1, JP2.10, JP3.2, JP4.2, QG1.8 (VCC), QG2.8 (VCC), R1.2, R6.2, R13.2, R14.2, R15.2, TP2.TP, U$1.4 (VOUT), U$6.VBACKUP, U$6.VCC, U$7.E/D, U$7.VDD, U$8.E/D, U$8.VDD
WP_EEPROM: IC1.5 (!WP), R14.1

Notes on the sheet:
Shorten two present pins!
Power
Timing_Clock
FPGA I/O Pins
FPGA_to_EEPROM
Microcontroller
JTAG
Friendship_Connector
FPGA_SPI_Clock
Testpoints
Optional

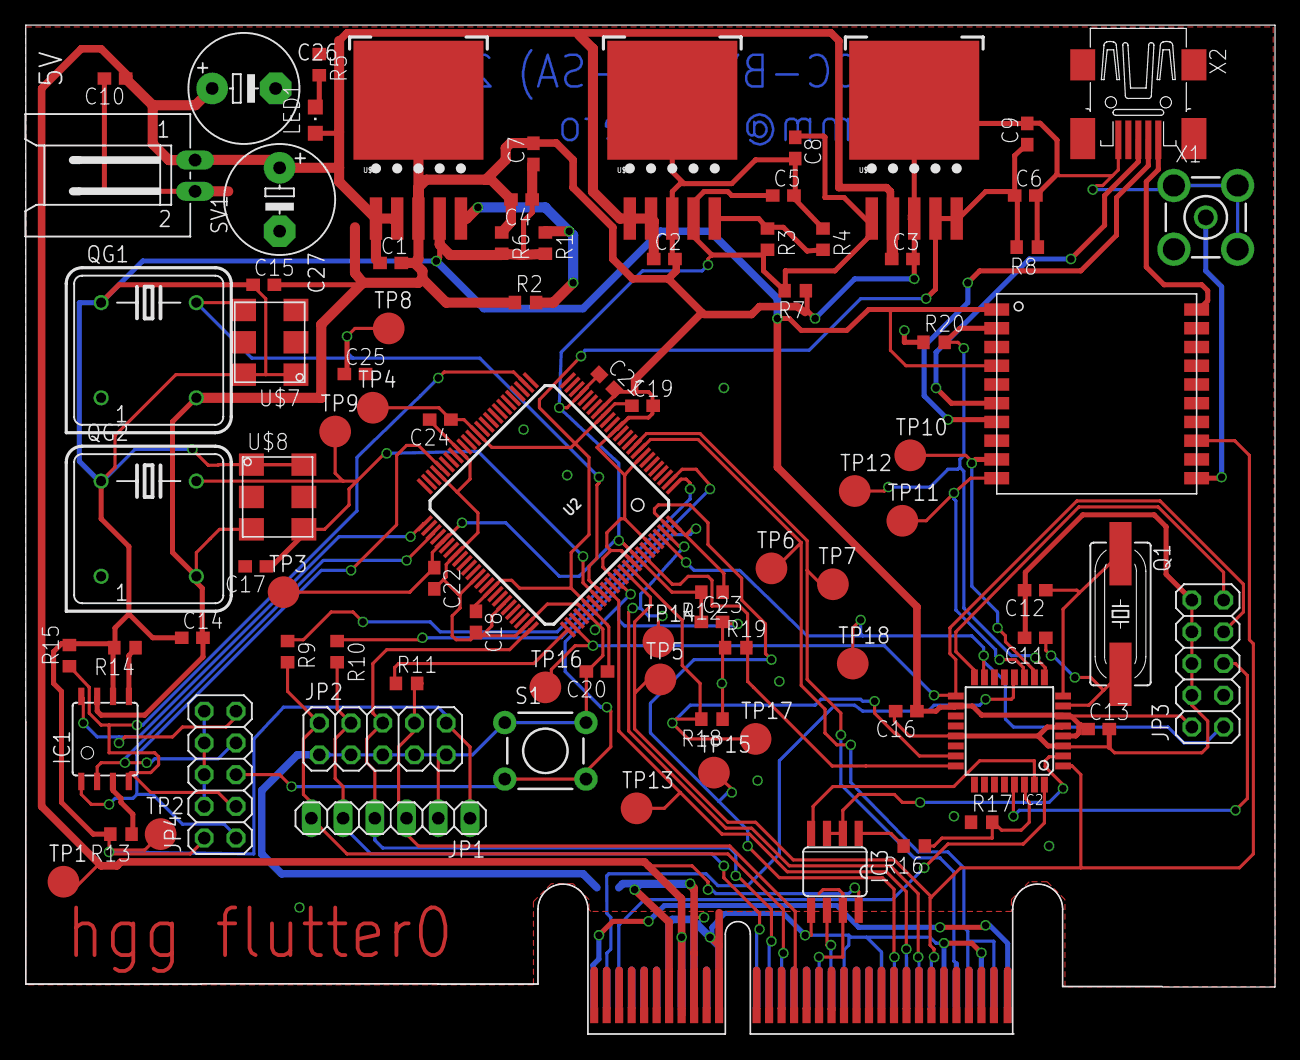
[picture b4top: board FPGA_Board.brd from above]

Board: 2 copper layers, 100.0 x 80.8 mm, 89 parts (0 on the bottom side), 54 nets.

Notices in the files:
hgg/modules/braeburn/braeburn1/braeburn1.brd:
CC by-nc-sa
hgg/modules/flutter/hardware/FPGA_Board.brd:
(CC-BY-NC-SA) 2012
hgg/modules/friendship/friendship_v0/frienship_1.brd:
(CC-BY-NC-SA 3.0) 2012
